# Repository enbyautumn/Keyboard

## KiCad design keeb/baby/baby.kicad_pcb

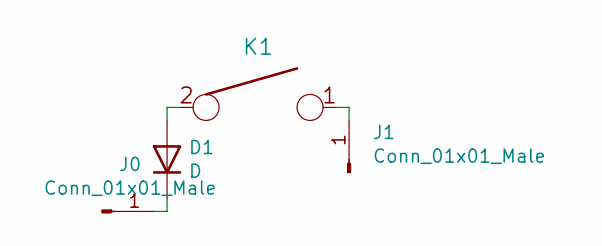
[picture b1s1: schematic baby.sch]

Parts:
D1: D; D_SOD123_axial
J0, J1: Conn_01x01_Male; TestPoint_Pad_2.0x2.0mm
K1: KEYSW; Kailh_socket_MX

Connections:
unnamed: D1.1 (K), J0.1
unnamed: D1.2 (A), K1.2
unnamed: J1.1, K1.1

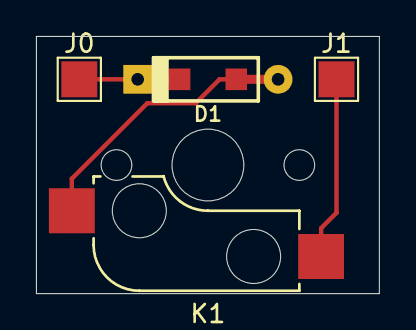
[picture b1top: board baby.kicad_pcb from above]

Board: 2 copper layers, 19.0 x 14.3 mm, 4 parts (1 on the bottom side), 3 nets.

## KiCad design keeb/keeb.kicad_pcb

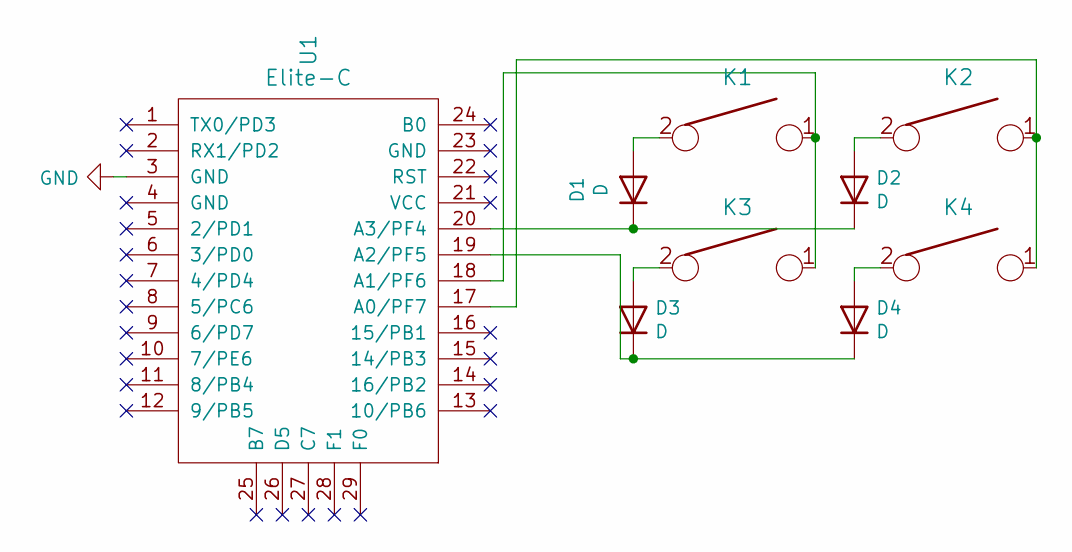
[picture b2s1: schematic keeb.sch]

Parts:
D1, D2, D3, D4: D; D_SOD123_axial
K1, K2, K3, K4: KEYSW; Mx_Alps_100
U1: Elite-C

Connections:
GND: U1.3 (GND)
unnamed: D1.1 (K), D2.1 (K), U1.20 (A3/PF4)
unnamed: D1.2 (A), K1.2
unnamed: D2.2 (A), K2.2
unnamed: D3.1 (K), D4.1 (K), U1.19 (A2/PF5)
unnamed: D3.2 (A), K3.2
unnamed: D4.2 (A), K4.2
unnamed: K1.1, K3.1, U1.18 (A1/PF6)
unnamed: K2.1, K4.1, U1.17 (A0/PF7)

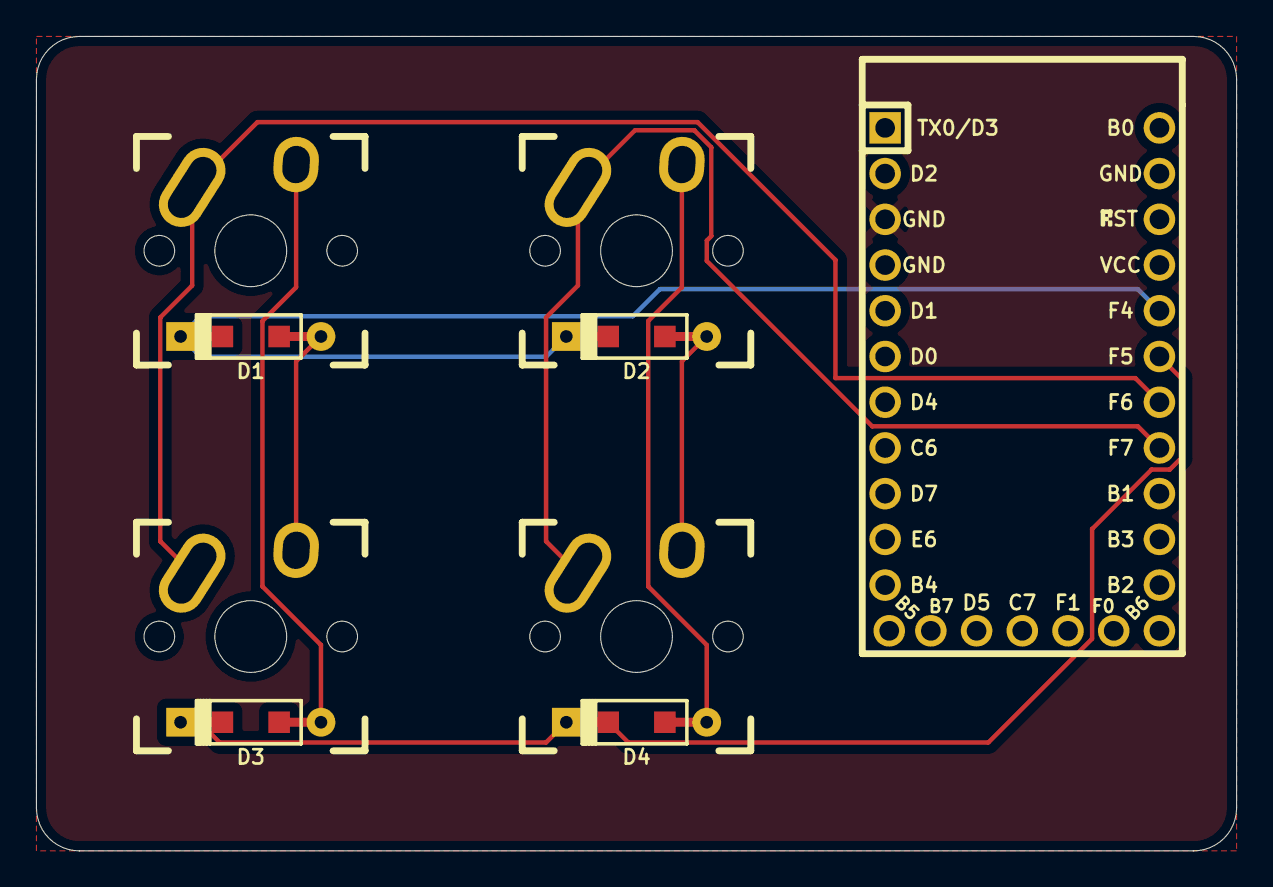
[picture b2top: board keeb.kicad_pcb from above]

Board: 2 copper layers, 66.7 x 45.2 mm, 9 parts (0 on the bottom side), 8 nets.

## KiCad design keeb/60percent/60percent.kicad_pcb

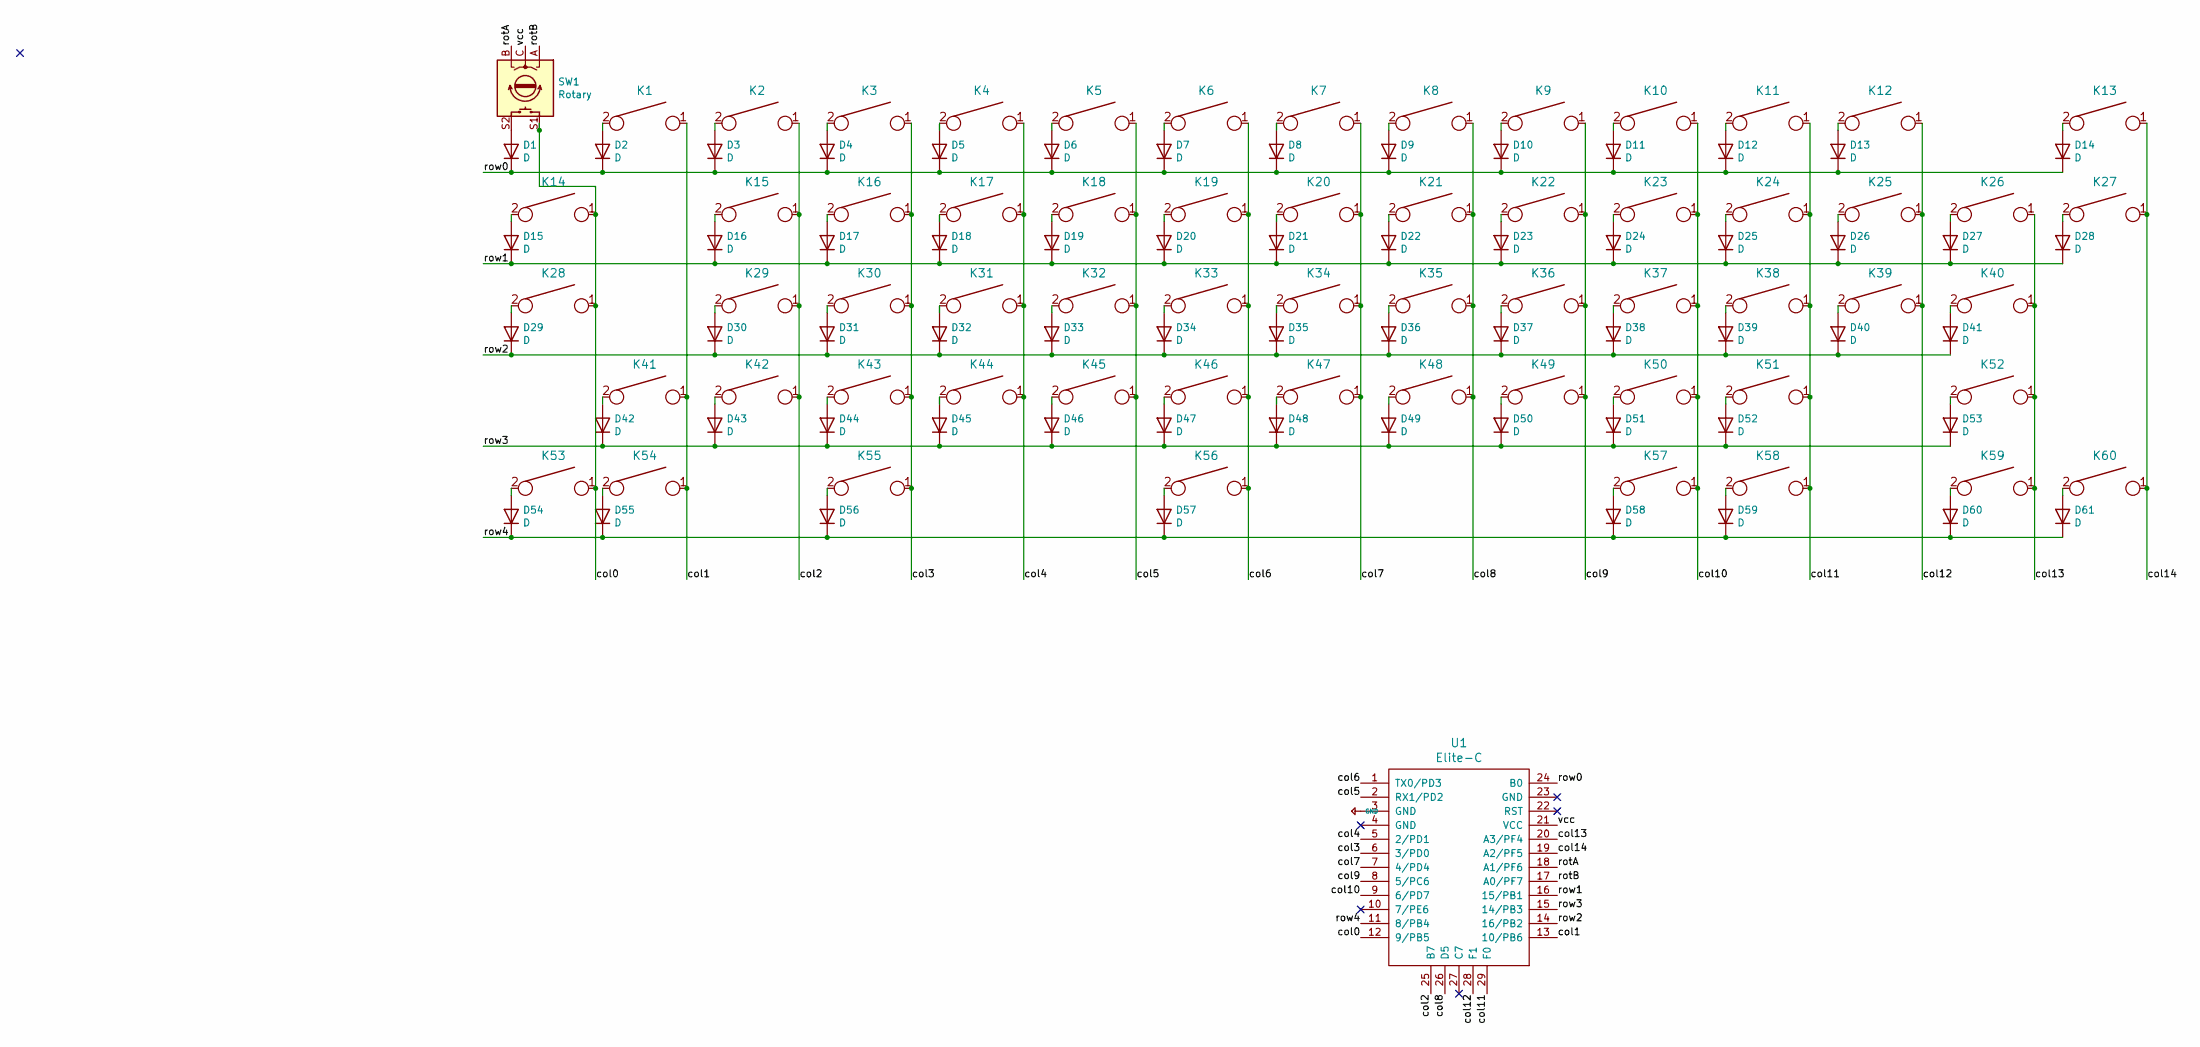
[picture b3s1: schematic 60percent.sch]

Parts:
D1, D2, D3, D4, D5, D6, D7, D8, D9, D10, D11, D12, D13, D14, D15, D16, D17, D18, D19, D20, D21, D22, D23, D24, D25, D26, D27, D28, D29, D30, D31, D32, D33, D34, D35, D36, D37, D38, D39, D40, D41, D42, D43, D44, D45, D46, D47, D48, D49, D50, D51, D52, D53, D54, D55, D56, D57, D58, D59, D60, D61: D; D_SOD123_axial
K1, K2, K3, K4, K5, K6, K7, K8, K9, K10, K11, K12, K15, K16, K17, K18, K19, K20, K21, K22, K23, K24, K25, K26, K29, K30, K31, K32, K33, K34, K35, K36, K37, K38, K39, K42, K43, K44, K45, K46, K47, K48, K49, K50, K51: KEYSW; SW_Hotswap_Kailh_1.00u
K13: KEYSW; SW_Hotswap_Kailh_2.00u
K14, K27: KEYSW; SW_Hotswap_Kailh_1.50u
K28: KEYSW; SW_Hotswap_Kailh_1.75u
K40, K41: KEYSW; SW_Hotswap_Kailh_2.25u
K52: KEYSW; SW_Hotswap_Kailh_2.75u
K53, K54, K55, K57, K58, K59, K60: KEYSW; SW_Hotswap_Kailh_1.25u
K56: KEYSW; SW_Hotswap_Kailh_6.25u
SW1: Rotary; RotaryEncoder_Alps_EC11E-Switch_Vertical_H20mm
U1: Elite-C

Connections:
+5V: U1.3 (GND)
/col0: K14.1, K28.1, K53.1, SW1.S1, U1.12 (9/PB5)
/col1: K1.1, K41.1, K54.1, U1.13 (10/PB6)
/col2: K2.1, K15.1, K29.1, K42.1, U1.25 (B7)
/col3: K3.1, K16.1, K30.1, K43.1, K55.1, U1.6 (3/PD0)
/col4: K4.1, K17.1, K31.1, K44.1, U1.5 (2/PD1)
/col5: K5.1, K18.1, K32.1, K45.1, U1.2 (RX1/PD2)
/col6: K6.1, K19.1, K33.1, K46.1, K56.1, U1.1 (TX0/PD3)
/col7: K7.1, K20.1, K34.1, K47.1, U1.7 (4/PD4)
/col8: K8.1, K21.1, K35.1, K48.1, U1.26 (D5)
/col9: K9.1, K22.1, K36.1, K49.1, U1.8 (5/PC6)
/col10: K10.1, K23.1, K37.1, K50.1, K57.1, U1.9 (6/PD7)
/col11: K11.1, K24.1, K38.1, K51.1, K58.1, U1.29 (F0)
/col12: K12.1, K25.1, K39.1, U1.28 (F1)
/col13: K26.1, K40.1, K52.1, K59.1, U1.20 (A3/PF4)
/col14: K13.1, K27.1, K60.1, U1.19 (A2/PF5)
/rotA: SW1.B, U1.18 (A1/PF6)
/rotB: SW1.A, U1.17 (A0/PF7)
/row0: D1.1 (K), D2.1 (K), D3.1 (K), D4.1 (K), D5.1 (K), D6.1 (K), D7.1 (K), D8.1 (K), D9.1 (K), D10.1 (K), D11.1 (K), D12.1 (K), D13.1 (K), D14.1 (K), U1.24 (B0)
/row1: D15.1 (K), D16.1 (K), D17.1 (K), D18.1 (K), D19.1 (K), D20.1 (K), D21.1 (K), D22.1 (K), D23.1 (K), D24.1 (K), D25.1 (K), D26.1 (K), D27.1 (K), D28.1 (K), U1.16 (15/PB1)
/row2: D29.1 (K), D30.1 (K), D31.1 (K), D32.1 (K), D33.1 (K), D34.1 (K), D35.1 (K), D36.1 (K), D37.1 (K), D38.1 (K), D39.1 (K), D40.1 (K), D41.1 (K), U1.14 (16/PB2)
/row3: D42.1 (K), D43.1 (K), D44.1 (K), D45.1 (K), D46.1 (K), D47.1 (K), D48.1 (K), D49.1 (K), D50.1 (K), D51.1 (K), D52.1 (K), D53.1 (K), U1.15 (14/PB3)
/row4: D54.1 (K), D55.1 (K), D56.1 (K), D57.1 (K), D58.1 (K), D59.1 (K), D60.1 (K), D61.1 (K), U1.11 (8/PB4)
/vcc: SW1.C, U1.21 (VCC)
unnamed: D1.2 (A), SW1.S2
unnamed: D2.2 (A), K1.2
unnamed: D3.2 (A), K2.2
unnamed: D4.2 (A), K3.2
unnamed: D5.2 (A), K4.2
unnamed: D6.2 (A), K5.2
unnamed: D7.2 (A), K6.2
unnamed: D8.2 (A), K7.2
unnamed: D9.2 (A), K8.2
unnamed: D10.2 (A), K9.2
unnamed: D11.2 (A), K10.2
unnamed: D12.2 (A), K11.2
unnamed: D13.2 (A), K12.2
unnamed: D14.2 (A), K13.2
unnamed: D15.2 (A), K14.2
unnamed: D16.2 (A), K15.2
unnamed: D17.2 (A), K16.2
unnamed: D18.2 (A), K17.2
unnamed: D19.2 (A), K18.2
unnamed: D20.2 (A), K19.2
unnamed: D21.2 (A), K20.2
unnamed: D22.2 (A), K21.2
unnamed: D23.2 (A), K22.2
unnamed: D24.2 (A), K23.2
unnamed: D25.2 (A), K24.2
unnamed: D26.2 (A), K25.2
unnamed: D27.2 (A), K26.2
unnamed: D28.2 (A), K27.2
unnamed: D29.2 (A), K28.2
unnamed: D30.2 (A), K29.2
unnamed: D31.2 (A), K30.2
unnamed: D32.2 (A), K31.2
unnamed: D33.2 (A), K32.2
unnamed: D34.2 (A), K33.2
unnamed: D35.2 (A), K34.2
unnamed: D36.2 (A), K35.2
unnamed: D37.2 (A), K36.2
unnamed: D38.2 (A), K37.2
unnamed: D39.2 (A), K38.2
unnamed: D40.2 (A), K39.2
unnamed: D41.2 (A), K40.2
unnamed: D42.2 (A), K41.2
unnamed: D43.2 (A), K42.2
unnamed: D44.2 (A), K43.2
unnamed: D45.2 (A), K44.2
unnamed: D46.2 (A), K45.2
unnamed: D47.2 (A), K46.2
unnamed: D48.2 (A), K47.2
unnamed: D49.2 (A), K48.2
unnamed: D50.2 (A), K49.2
unnamed: D51.2 (A), K50.2
unnamed: D52.2 (A), K51.2
unnamed: D53.2 (A), K52.2
unnamed: D54.2 (A), K53.2
unnamed: D55.2 (A), K54.2
unnamed: D56.2 (A), K55.2
unnamed: D57.2 (A), K56.2
unnamed: D58.2 (A), K57.2
unnamed: D59.2 (A), K58.2
unnamed: D60.2 (A), K59.2
unnamed: D61.2 (A), K60.2

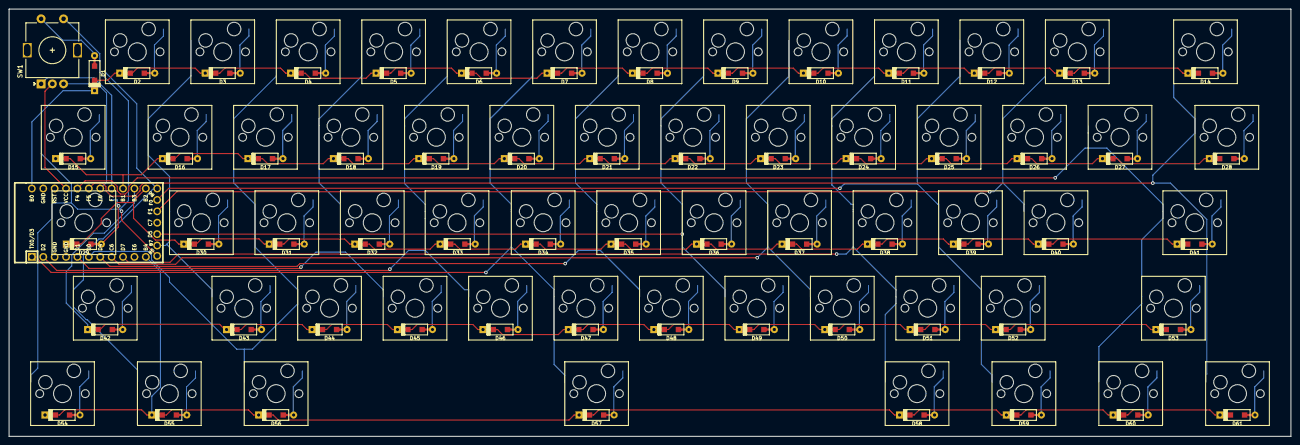
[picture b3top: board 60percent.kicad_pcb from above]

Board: 2 copper layers, 285.8 x 95.2 mm, 123 parts (0 on the bottom side), 84 nets.

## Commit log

2021-02-14 i did the do
2021-02-16 i have no idea what the fuck i am doing
2021-03-16 okay
